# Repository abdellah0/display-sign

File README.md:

display-sign
============

2 Digit 7 Segment Arduino Countdown Sign using 12v LED Strip

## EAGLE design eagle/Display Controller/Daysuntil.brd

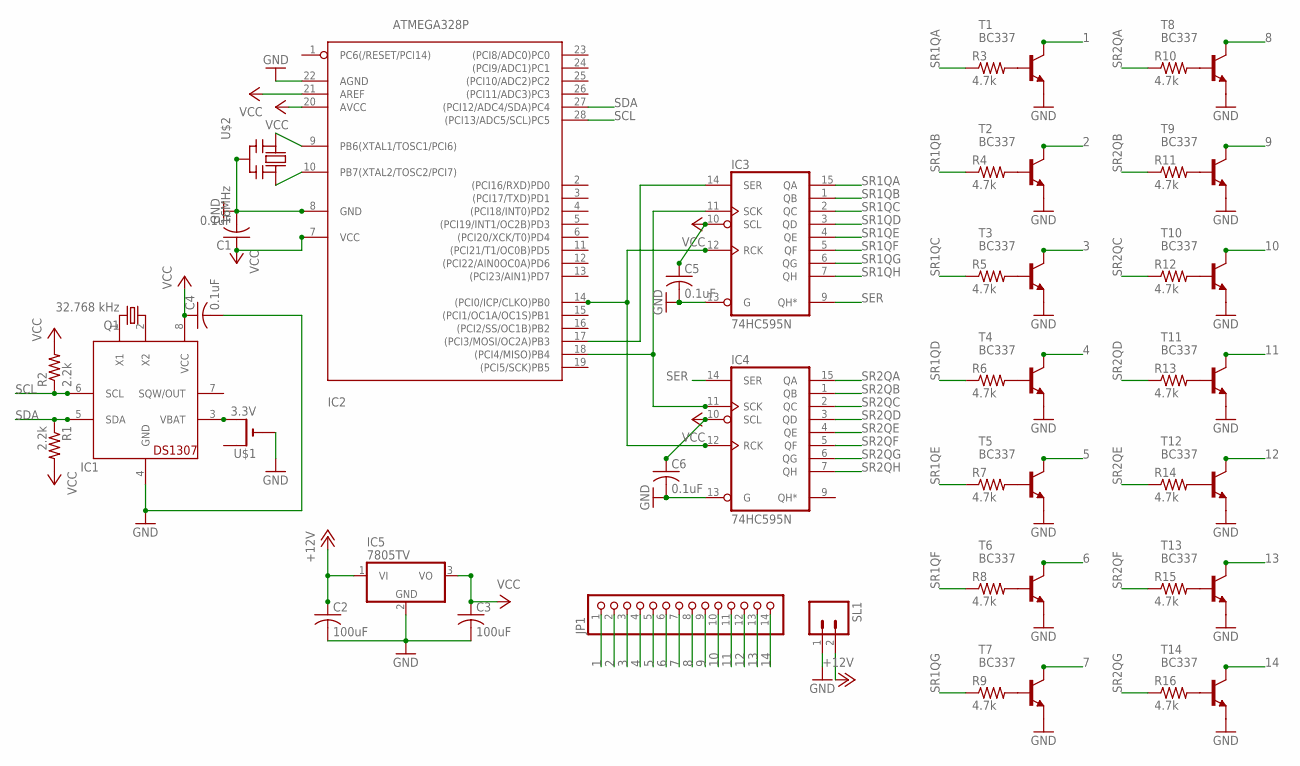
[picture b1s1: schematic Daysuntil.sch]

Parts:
C1, C4, C5, C6: 0.1uF; C025-030X050
C2, C3: 100uF; C050-050X075
IC1: DS1307; DIL08
IC2: ATMEGA328P; DIL28-3
IC3, IC4: 74HC595N; DIL16
IC5: 7805TV; TO220V
JP1: PINHD-1X14; 1X14
Q1: 32.768 kHz; TC38H
R1, R2: 2.2k; 0309V
R3, R4, R5, R6, R7, R8, R9, R10, R11, R12, R13, R14, R15, R16: 4.7k; 0309V
SL1: M02; 02P
T1, T2, T3, T4, T5, T6, T7, T8, T9, T10, T11, T12, T13, T14: BC337; TO92
U$1: 3.3V; CR1220-THM
U$2: 16MHz; CERM_OSC

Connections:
1: JP1.1, T1.3 (C)
2: JP1.2, T2.3 (C)
3: JP1.3, T3.3 (C)
4: JP1.4, T4.3 (C)
5: JP1.5, T5.3 (C)
6: JP1.6, T6.3 (C)
7: JP1.7, T7.3 (C)
8: JP1.8, T8.3 (C)
9: JP1.9, T9.3 (C)
10: JP1.10, T10.3 (C)
11: JP1.11, T11.3 (C)
12: JP1.12, T12.3 (C)
13: JP1.13, T13.3 (C)
14: JP1.14, T14.3 (C)
+12V: C2.1, IC5.1 (VI), SL1.2
GND: C1.2, C2.2, C3.2, C4.2, C5.2, C6.2, IC1.4 (GND), IC2.8 (GND), IC2.22 (AGND), IC3.8 (GND), IC3.13 (G), IC4.8 (GND), IC4.13 (G), IC5.2 (GND), SL1.1, T1.1 (E), T2.1 (E), T3.1 (E), T4.1 (E), T5.1 (E), T6.1 (E), T7.1 (E), T8.1 (E), T9.1 (E), T10.1 (E), T11.1 (E), T12.1 (E), T13.1 (E), T14.1 (E), U$1.-, U$2.P$2 (GND)
unnamed: R3.2, T1.2 (B)
unnamed: IC2.17 ((PCI3/MOSI/OC2A)PB3), IC3.14 (SER)
unnamed: IC1.3 (VBAT), U$1.+2 (+1)
unnamed: IC1.1 (X1), Q1.2
unnamed: IC1.2 (X2), Q1.1
unnamed: IC2.18 ((PCI4/MISO)PB4), IC3.11 (SCK), IC4.11 (SCK)
unnamed: IC2.14 ((PCI0/ICP/CLKO)PB0), IC3.12 (RCK), IC4.12 (RCK)
unnamed: IC2.9 (PB6(XTAL1/TOSC1/PCI6)), U$2.P$1 (IN)
unnamed: IC2.10 (PB7(XTAL2/TOSC2/PCI7)), U$2.P$3 (OUT)
unnamed: R4.2, T2.2 (B)
unnamed: R5.2, T3.2 (B)
unnamed: R6.2, T4.2 (B)
unnamed: R7.2, T5.2 (B)
unnamed: R8.2, T6.2 (B)
unnamed: R9.2, T7.2 (B)
unnamed: R10.2, T8.2 (B)
unnamed: R11.2, T9.2 (B)
unnamed: R12.2, T10.2 (B)
unnamed: R13.2, T11.2 (B)
unnamed: R14.2, T12.2 (B)
unnamed: R15.2, T13.2 (B)
unnamed: R16.2, T14.2 (B)
SCL: IC1.6 (SCL), IC2.28 ((PCI13/ADC5/SCL)PC5), R2.1
SDA: IC1.5 (SDA), IC2.27 ((PCI12/ADC4/SDA)PC4), R1.1
SER: IC3.9 (QH*), IC4.14 (SER)
SR1QA: IC3.15 (QA), R3.1
SR1QB: IC3.1 (QB), R4.1
SR1QC: IC3.2 (QC), R5.1
SR1QD: IC3.3 (QD), R6.1
SR1QE: IC3.4 (QE), R7.1
SR1QF: IC3.5 (QF), R8.1
SR1QG: IC3.6 (QG), R9.1
SR1QH: IC3.7 (QH)
SR2QA: IC4.15 (QA), R10.1
SR2QB: IC4.1 (QB), R11.1
SR2QC: IC4.2 (QC), R12.1
SR2QD: IC4.3 (QD), R13.1
SR2QE: IC4.4 (QE), R14.1
SR2QF: IC4.5 (QF), R15.1
SR2QG: IC4.6 (QG), R16.1
SR2QH: IC4.7 (QH)
VCC: C1.1, C3.1, C4.1, C5.1, C6.1, IC1.8 (VCC), IC2.7 (VCC), IC2.20 (AVCC), IC2.21 (AREF), IC3.10 (SCL), IC3.16 (VCC), IC4.10 (SCL), IC4.16 (VCC), IC5.3 (VO), R1.2, R2.2

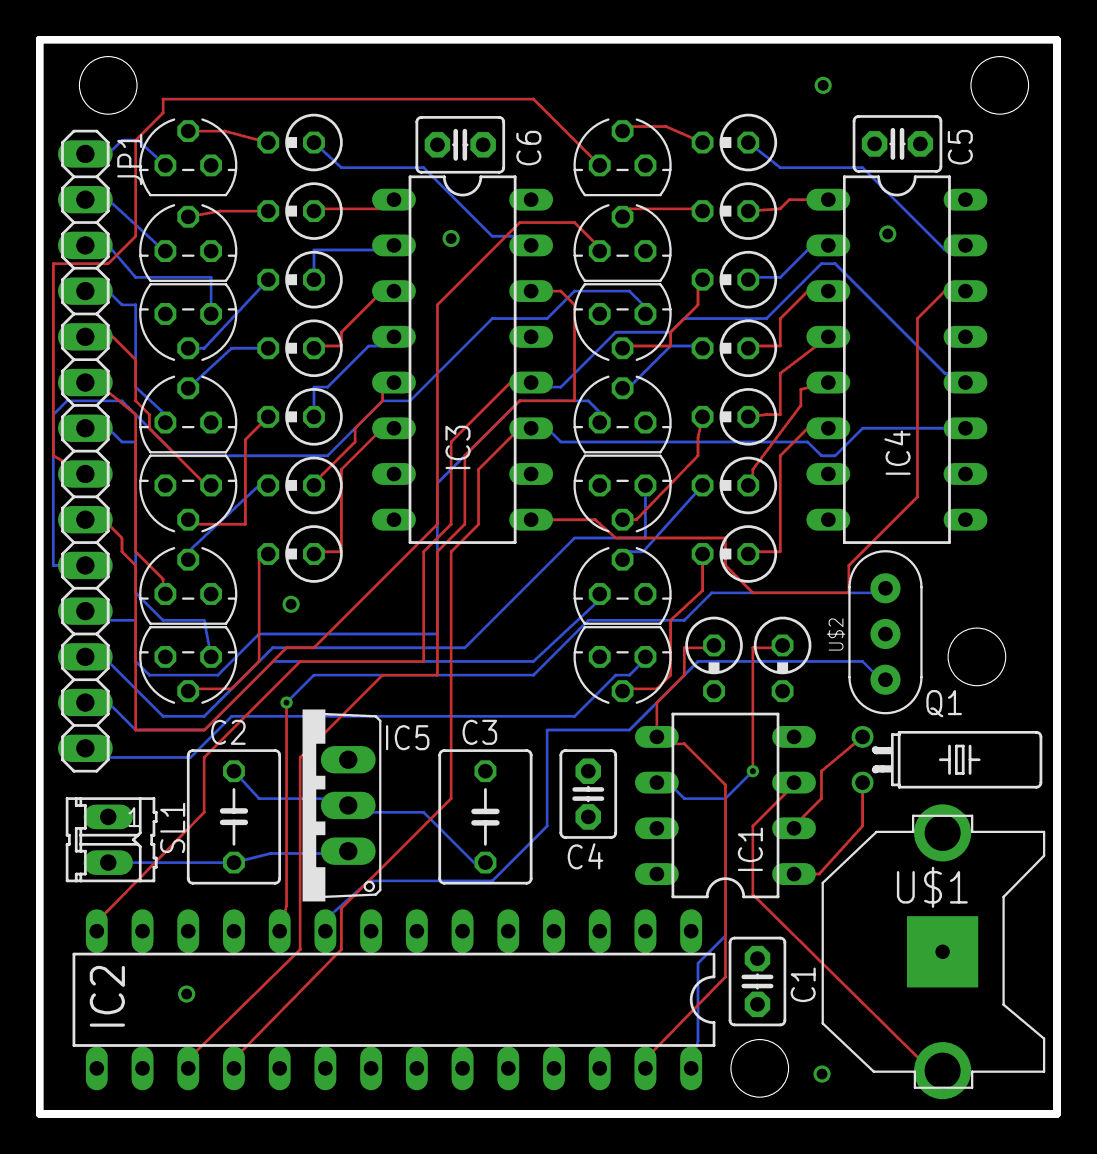
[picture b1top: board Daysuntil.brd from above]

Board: 2 copper layers, 56.5 x 59.7 mm, 47 parts (0 on the bottom side), 56 nets.

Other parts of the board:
U$3: BITMAP-SLEIGHT

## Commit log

2013-01-10 add file structure
2013-01-10 removed some files
2013-01-10 add arduino
2013-01-25 added loading animation
2013-01-25 updated board config
2013-01-26 finalized board design
2013-01-27 final board design with CAM files
2013-04-12 upload code v1 and fix ground on 7805 in board schematic.
2013-04-26 update code to include serial output for debug
